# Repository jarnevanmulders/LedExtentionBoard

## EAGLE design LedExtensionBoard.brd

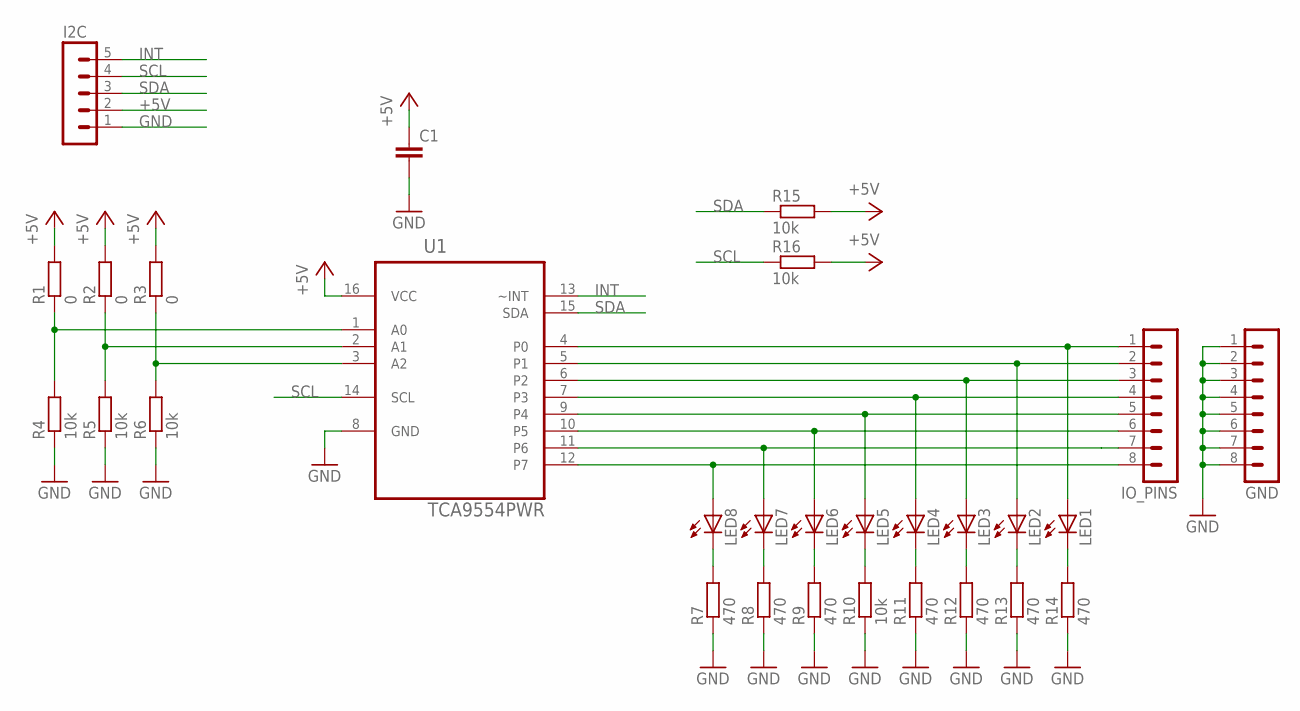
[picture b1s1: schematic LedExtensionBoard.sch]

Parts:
C1: C-EUC0805; C0805
GND: MA08-1
I2C: MA05-1
IO_PINS: MA08-1
LED1, LED2, LED3, LED4, LED5, LED6, LED7, LED8: LEDSML0805; SML0805
R1, R2, R3: 0; M1206
R4, R5, R6, R10, R15, R16: 10k; M0805
R7, R8, R9, R11, R12, R13, R14: 470; M0805
U1: TCA9554PWR; SOP65P640X120-16N

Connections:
+5V: C1.1, I2C.2, R1.2, R2.2, R3.2, R15.2, R16.2, U1.16 (VCC)
GND: C1.2, GND.1, GND.2, GND.3, GND.4, GND.5, GND.6, GND.7, GND.8, I2C.1, R4.1, R5.1, R6.1, R7.1, R8.1, R9.1, R10.1, R11.1, R12.1, R13.1, R14.1, U1.8 (GND)
INT: I2C.5, U1.13 (~INT)
unnamed: IO_PINS.8, LED8.A, U1.12 (P7)
unnamed: IO_PINS.7, LED7.A, U1.11 (P6)
unnamed: IO_PINS.6, LED6.A, U1.10 (P5)
unnamed: IO_PINS.5, LED5.A, U1.9 (P4)
unnamed: IO_PINS.4, LED4.A, U1.7 (P3)
unnamed: IO_PINS.3, LED3.A, U1.6 (P2)
unnamed: IO_PINS.2, LED2.A, U1.5 (P1)
unnamed: IO_PINS.1, LED1.A, U1.4 (P0)
unnamed: LED8.C, R7.2
unnamed: LED7.C, R8.2
unnamed: LED6.C, R9.2
unnamed: R1.1, R4.2, U1.1 (A0)
unnamed: R2.1, R5.2, U1.2 (A1)
unnamed: R3.1, R6.2, U1.3 (A2)
unnamed: LED5.C, R10.2
unnamed: LED4.C, R11.2
unnamed: LED3.C, R12.2
unnamed: LED2.C, R13.2
unnamed: LED1.C, R14.2
SCL: I2C.4, R16.1, U1.14 (SCL)
SDA: I2C.3, R15.1, U1.15 (SDA)

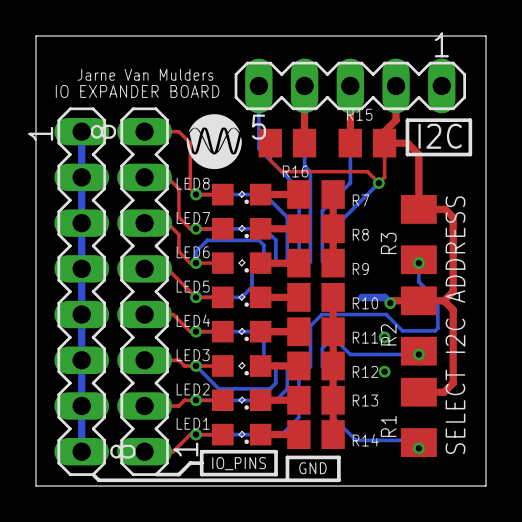
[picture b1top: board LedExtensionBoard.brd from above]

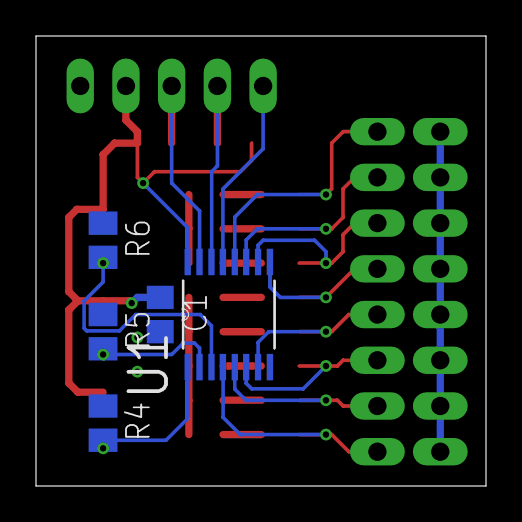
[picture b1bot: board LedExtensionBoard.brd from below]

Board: 2 copper layers, 25.0 x 25.0 mm, 29 parts (5 on the bottom side), 24 nets.

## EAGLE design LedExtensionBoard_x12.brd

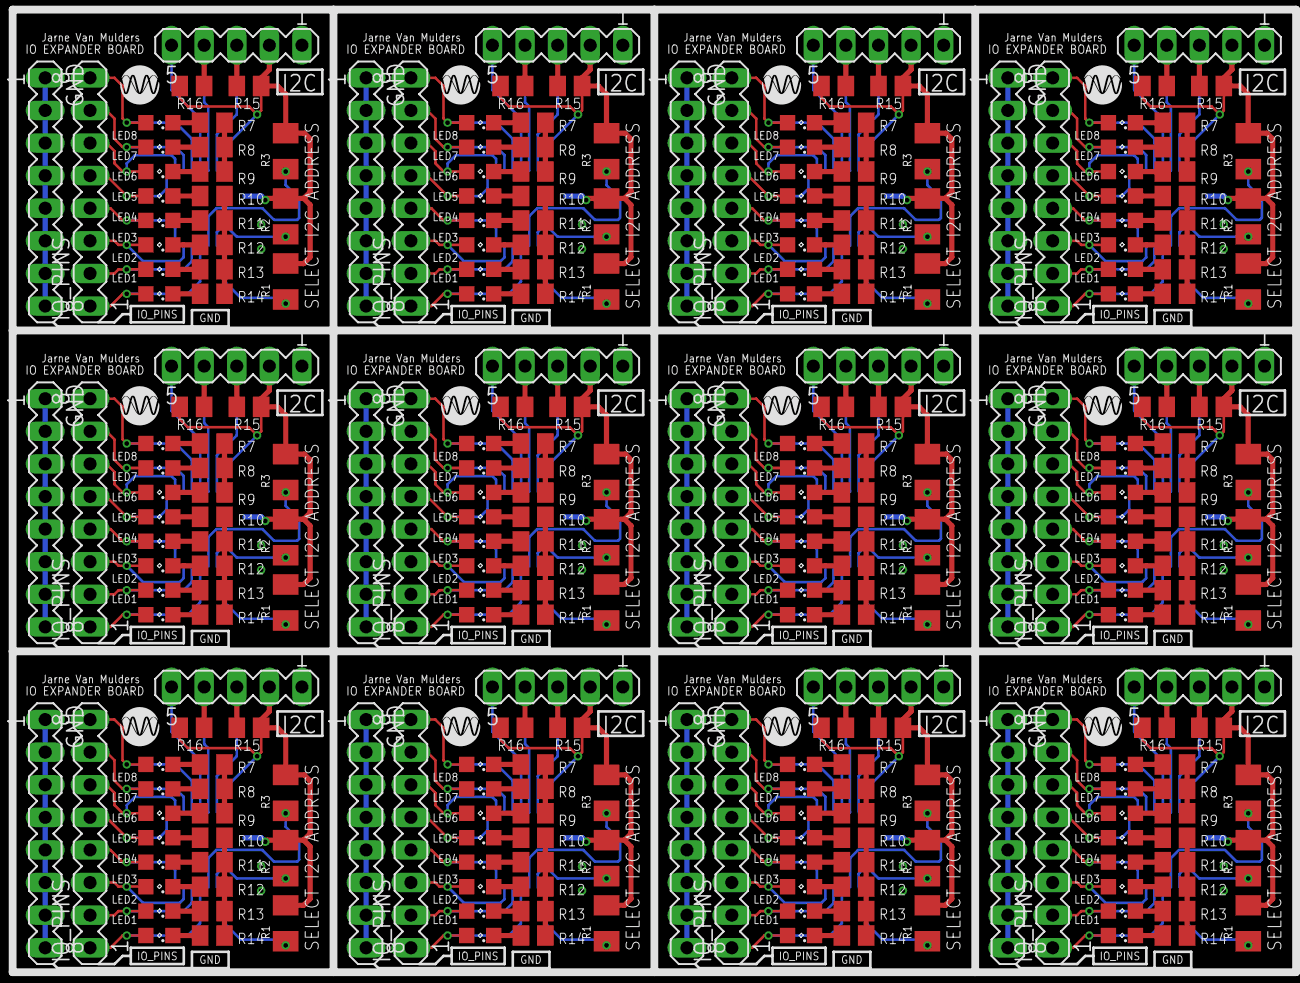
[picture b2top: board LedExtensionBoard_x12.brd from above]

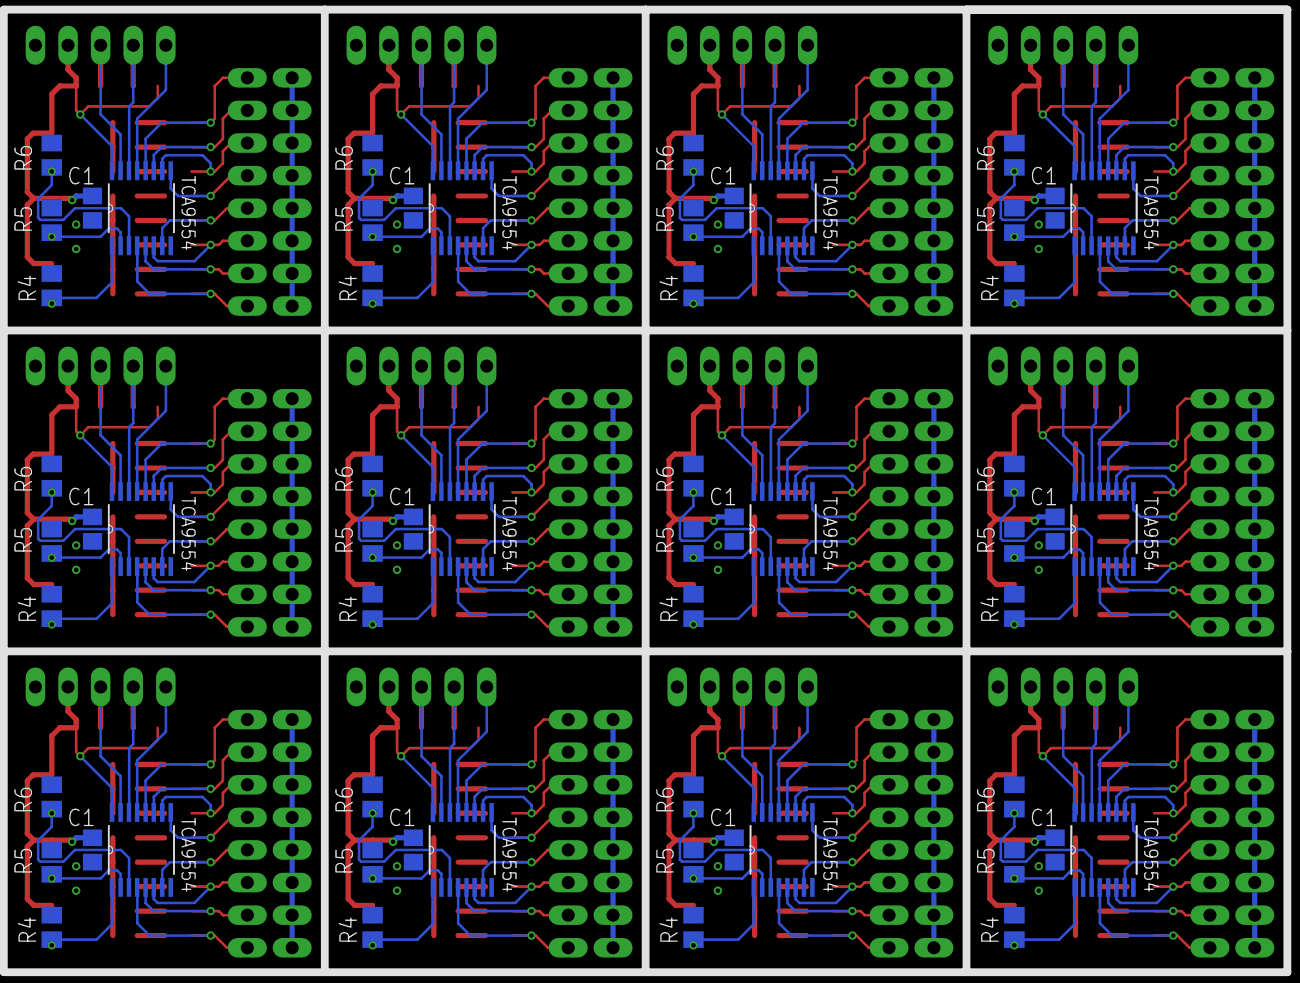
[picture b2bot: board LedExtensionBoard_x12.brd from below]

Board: 2 copper layers, 348 parts (60 on the bottom side), 288 nets.

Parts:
C1, C2, C3, C4, C5, C6, C7, C8, C9, C10, C11, C12: C0805
GND, GND1, GND2, GND3, GND4, GND5, GND6, GND7, GND8, GND9, GND10, GND11: MA08-1
I2C, I2C1, I2C2, I2C3, I2C4, I2C5, I2C6, I2C7, I2C8, I2C9, I2C10, I2C11: MA05-1
IO_PINS, IO_PINS1, IO_PINS2, IO_PINS3, IO_PINS4, IO_PINS5, IO_PINS6, IO_PINS7, IO_PINS8, IO_PINS9, IO_PINS10, IO_PINS11: MA08-1
LED1, LED2, LED3, LED4, LED5, LED6, LED7, LED8, LED9, LED10, LED11, LED12, LED13, LED14, LED15, LED16, LED17, LED18, LED19, LED20, LED21, LED22, LED23, LED24, LED25, LED26, LED27, LED28, LED29, LED30, LED31, LED32, LED33, LED34, LED35, LED36, LED37, LED38, LED39, LED40, LED41, LED42, LED43, LED44, LED45, LED46, LED47, LED48, LED49, LED50, LED51, LED52, LED53, LED54, LED55, LED56, LED57, LED58, LED59, LED60, LED61, LED62, LED63, LED64, LED65, LED66, LED67, LED68, LED69, LED70, LED71, LED72, LED73, LED74, LED75, LED76, LED77, LED78, LED79, LED80, LED81, LED82, LED83, LED84, LED85, LED86, LED87, LED88, LED89, LED90, LED91, LED92, LED93, LED94, LED95, LED96: SML0805
R1, R2, R3, R17, R23, R24, R33, R39, R40, R49, R55, R56, R65, R71, R72, R81, R87, R88, R97, R103, R104, R113, R119, R120, R129, R135, R136, R145, R151, R152, R161, R167, R168, R177, R183, R184: 0; M1206
R4, R5, R6, R10, R15, R16, R18, R25, R26, R27, R31, R32, R34, R41, R42, R43, R47, R48, R50, R57, R58, R59, R63, R64, R66, R73, R74, R75, R79, R80, R82, R89, R90, R91, R95, R96, R98, R105, R106, R107, R111, R112, R114, R121, R122, R123, R127, R128, R130, R137, R138, R139, R143, R144, R146, R153, R154, R155, R159, R160, R162, R169, R170, R171, R175, R176, R178, R185, R186, R187, R191, R192: 10k; M0805
R7, R8, R9, R11, R12, R13, R14, R19, R20, R21, R22, R28, R29, R30, R35, R36, R37, R38, R44, R45, R46, R51, R52, R53, R54, R60, R61, R62, R67, R68, R69, R70, R76, R77, R78, R83, R84, R85, R86, R92, R93, R94, R99, R100, R101, R102, R108, R109, R110, R115, R116, R117, R118, R124, R125, R126, R131, R132, R133, R134, R140, R141, R142, R147, R148, R149, R150, R156, R157, R158, R163, R164, R165, R166, R172, R173, R174, R179, R180, R181, R182, R188, R189, R190: 470; M0805
U1, U2, U3, U4, U5, U6, U7, U8, U9, U10, U11, U12: TCA9554PWR; SOP65P640X120-16N

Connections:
+5V: C1.1, I2C.2, R1.2, R2.2, R3.2, R15.2, R16.2, U1.16
+5V1: C2.1, I2C1.2, R17.2, R23.2, R24.2, R31.2, R32.2, U2.16
+5V2: C3.1, I2C2.2, R33.2, R39.2, R40.2, R47.2, R48.2, U3.16
+5V3: C4.1, I2C3.2, R49.2, R55.2, R56.2, R63.2, R64.2, U4.16
+5V4: C5.1, I2C4.2, R65.2, R71.2, R72.2, R79.2, R80.2, U5.16
+5V5: C6.1, I2C5.2, R81.2, R87.2, R88.2, R95.2, R96.2, U6.16
+5V6: C7.1, I2C6.2, R97.2, R103.2, R104.2, R111.2, R112.2, U7.16
+5V7: C8.1, I2C7.2, R113.2, R119.2, R120.2, R127.2, R128.2, U8.16
+5V8: C9.1, I2C8.2, R129.2, R135.2, R136.2, R143.2, R144.2, U9.16
+5V9: C10.1, I2C9.2, R145.2, R151.2, R152.2, R159.2, R160.2, U10.16
+5V10: C11.1, I2C10.2, R161.2, R167.2, R168.2, R175.2, R176.2, U11.16
+5V11: C12.1, I2C11.2, R177.2, R183.2, R184.2, R191.2, R192.2, U12.16
GND: C1.2, GND.1, GND.2, GND.3, GND.4, GND.5, GND.6, GND.7, GND.8, I2C.1, R4.1, R5.1, R6.1, R7.1, R8.1, R9.1, R10.1, R11.1, R12.1, R13.1, R14.1, U1.8
GND1: C2.2, GND1.1, GND1.2, GND1.3, GND1.4, GND1.5, GND1.6, GND1.7, GND1.8, I2C1.1, R18.1, R19.1, R20.1, R21.1, R22.1, R25.1, R26.1, R27.1, R28.1, R29.1, R30.1, U2.8
GND2: C3.2, GND2.1, GND2.2, GND2.3, GND2.4, GND2.5, GND2.6, GND2.7, GND2.8, I2C2.1, R34.1, R35.1, R36.1, R37.1, R38.1, R41.1, R42.1, R43.1, R44.1, R45.1, R46.1, U3.8
GND3: C4.2, GND3.1, GND3.2, GND3.3, GND3.4, GND3.5, GND3.6, GND3.7, GND3.8, I2C3.1, R50.1, R51.1, R52.1, R53.1, R54.1, R57.1, R58.1, R59.1, R60.1, R61.1, R62.1, U4.8
GND4: C5.2, GND4.1, GND4.2, GND4.3, GND4.4, GND4.5, GND4.6, GND4.7, GND4.8, I2C4.1, R66.1, R67.1, R68.1, R69.1, R70.1, R73.1, R74.1, R75.1, R76.1, R77.1, R78.1, U5.8
GND5: C6.2, GND5.1, GND5.2, GND5.3, GND5.4, GND5.5, GND5.6, GND5.7, GND5.8, I2C5.1, R82.1, R83.1, R84.1, R85.1, R86.1, R89.1, R90.1, R91.1, R92.1, R93.1, R94.1, U6.8
GND6: C7.2, GND6.1, GND6.2, GND6.3, GND6.4, GND6.5, GND6.6, GND6.7, GND6.8, I2C6.1, R98.1, R99.1, R100.1, R101.1, R102.1, R105.1, R106.1, R107.1, R108.1, R109.1, R110.1, U7.8
GND7: C8.2, GND7.1, GND7.2, GND7.3, GND7.4, GND7.5, GND7.6, GND7.7, GND7.8, I2C7.1, R114.1, R115.1, R116.1, R117.1, R118.1, R121.1, R122.1, R123.1, R124.1, R125.1, R126.1, U8.8
GND8: C9.2, GND8.1, GND8.2, GND8.3, GND8.4, GND8.5, GND8.6, GND8.7, GND8.8, I2C8.1, R130.1, R131.1, R132.1, R133.1, R134.1, R137.1, R138.1, R139.1, R140.1, R141.1, R142.1, U9.8
GND9: C10.2, GND9.1, GND9.2, GND9.3, GND9.4, GND9.5, GND9.6, GND9.7, GND9.8, I2C9.1, R146.1, R147.1, R148.1, R149.1, R150.1, R153.1, R154.1, R155.1, R156.1, R157.1, R158.1, U10.8
GND10: C11.2, GND10.1, GND10.2, GND10.3, GND10.4, GND10.5, GND10.6, GND10.7, GND10.8, I2C10.1, R162.1, R163.1, R164.1, R165.1, R166.1, R169.1, R170.1, R171.1, R172.1, R173.1, R174.1, U11.8
GND11: C12.2, GND11.1, GND11.2, GND11.3, GND11.4, GND11.5, GND11.6, GND11.7, GND11.8, I2C11.1, R178.1, R179.1, R180.1, R181.1, R182.1, R185.1, R186.1, R187.1, R188.1, R189.1, R190.1, U12.8
INT: I2C.5, U1.13
INT1: I2C1.5, U2.13
INT2: I2C2.5, U3.13
INT3: I2C3.5, U4.13
INT4: I2C4.5, U5.13
INT5: I2C5.5, U6.13
INT6: I2C6.5, U7.13
INT7: I2C7.5, U8.13
INT8: I2C8.5, U9.13
INT9: I2C9.5, U10.13
INT10: I2C10.5, U11.13
INT11: I2C11.5, U12.13
unnamed: IO_PINS.8, LED8.A, U1.12
unnamed: IO_PINS.7, LED7.A, U1.11
unnamed: IO_PINS.6, LED6.A, U1.10
unnamed: IO_PINS.5, LED5.A, U1.9
unnamed: IO_PINS.4, LED4.A, U1.7
unnamed: IO_PINS.3, LED3.A, U1.6
unnamed: IO_PINS.2, LED2.A, U1.5
unnamed: IO_PINS.1, LED1.A, U1.4
unnamed: LED8.C, R7.2
unnamed: LED7.C, R8.2
unnamed: LED6.C, R9.2
unnamed: R1.1, R4.2, U1.1
unnamed: R2.1, R5.2, U1.2
unnamed: R3.1, R6.2, U1.3
unnamed: LED5.C, R10.2
unnamed: LED4.C, R11.2
unnamed: LED3.C, R12.2
unnamed: LED2.C, R13.2
unnamed: LED1.C, R14.2
unnamed: IO_PINS1.8, LED16.A, U2.12
unnamed: IO_PINS1.7, LED15.A, U2.11
unnamed: IO_PINS1.6, LED14.A, U2.10
unnamed: IO_PINS1.5, LED13.A, U2.9
unnamed: IO_PINS1.4, LED12.A, U2.7
unnamed: IO_PINS1.3, LED11.A, U2.6
unnamed: IO_PINS1.2, LED10.A, U2.5
unnamed: IO_PINS1.1, LED9.A, U2.4
unnamed: R17.1, R25.2, U2.1
unnamed: R23.1, R26.2, U2.2
unnamed: R24.1, R27.2, U2.3
unnamed: LED16.C, R28.2
unnamed: LED15.C, R29.2
unnamed: LED14.C, R30.2
unnamed: LED13.C, R18.2
unnamed: LED12.C, R19.2
unnamed: LED11.C, R20.2
unnamed: LED10.C, R21.2
unnamed: LED9.C, R22.2
unnamed: IO_PINS2.8, LED24.A, U3.12
unnamed: IO_PINS2.7, LED23.A, U3.11
unnamed: IO_PINS2.6, LED22.A, U3.10
unnamed: IO_PINS2.5, LED21.A, U3.9
unnamed: IO_PINS2.4, LED20.A, U3.7
unnamed: IO_PINS2.3, LED19.A, U3.6
unnamed: IO_PINS2.2, LED18.A, U3.5
unnamed: IO_PINS2.1, LED17.A, U3.4
unnamed: R33.1, R41.2, U3.1
unnamed: R39.1, R42.2, U3.2
unnamed: R40.1, R43.2, U3.3
unnamed: LED24.C, R44.2
unnamed: LED23.C, R45.2
unnamed: LED22.C, R46.2
unnamed: LED21.C, R34.2
unnamed: LED20.C, R35.2
unnamed: LED19.C, R36.2
unnamed: LED18.C, R37.2
unnamed: LED17.C, R38.2
unnamed: IO_PINS3.8, LED32.A, U4.12
unnamed: IO_PINS3.7, LED31.A, U4.11
unnamed: IO_PINS3.6, LED30.A, U4.10
unnamed: IO_PINS3.5, LED29.A, U4.9
unnamed: IO_PINS3.4, LED28.A, U4.7
unnamed: IO_PINS3.3, LED27.A, U4.6
unnamed: IO_PINS3.2, LED26.A, U4.5
unnamed: IO_PINS3.1, LED25.A, U4.4
unnamed: R49.1, R57.2, U4.1
unnamed: R55.1, R58.2, U4.2
unnamed: R56.1, R59.2, U4.3
unnamed: LED32.C, R60.2
unnamed: LED31.C, R61.2
unnamed: LED30.C, R62.2
unnamed: LED29.C, R50.2
unnamed: LED28.C, R51.2
unnamed: LED27.C, R52.2
unnamed: LED26.C, R53.2
unnamed: LED25.C, R54.2
unnamed: IO_PINS4.8, LED40.A, U5.12
unnamed: IO_PINS4.7, LED39.A, U5.11
unnamed: IO_PINS4.6, LED38.A, U5.10
unnamed: IO_PINS4.5, LED37.A, U5.9
unnamed: IO_PINS4.4, LED36.A, U5.7
unnamed: IO_PINS4.3, LED35.A, U5.6
unnamed: IO_PINS4.2, LED34.A, U5.5
unnamed: IO_PINS4.1, LED33.A, U5.4
unnamed: R65.1, R73.2, U5.1
unnamed: R71.1, R74.2, U5.2
unnamed: R72.1, R75.2, U5.3
unnamed: LED40.C, R76.2
unnamed: LED39.C, R77.2
unnamed: LED38.C, R78.2
unnamed: LED37.C, R66.2
unnamed: LED36.C, R67.2
unnamed: LED35.C, R68.2
unnamed: LED34.C, R69.2
unnamed: LED33.C, R70.2
unnamed: IO_PINS5.8, LED48.A, U6.12
unnamed: IO_PINS5.7, LED47.A, U6.11
unnamed: IO_PINS5.6, LED46.A, U6.10
unnamed: IO_PINS5.5, LED45.A, U6.9
unnamed: IO_PINS5.4, LED44.A, U6.7
unnamed: IO_PINS5.3, LED43.A, U6.6
unnamed: IO_PINS5.2, LED42.A, U6.5
unnamed: IO_PINS5.1, LED41.A, U6.4
unnamed: R81.1, R89.2, U6.1
unnamed: R87.1, R90.2, U6.2
unnamed: R88.1, R91.2, U6.3
unnamed: LED48.C, R92.2
unnamed: LED47.C, R93.2
unnamed: LED46.C, R94.2
unnamed: LED45.C, R82.2
unnamed: LED44.C, R83.2
unnamed: LED43.C, R84.2
unnamed: LED42.C, R85.2
unnamed: LED41.C, R86.2
unnamed: IO_PINS6.8, LED56.A, U7.12
unnamed: IO_PINS6.7, LED55.A, U7.11
unnamed: IO_PINS6.6, LED54.A, U7.10
unnamed: IO_PINS6.5, LED53.A, U7.9
unnamed: IO_PINS6.4, LED52.A, U7.7
unnamed: IO_PINS6.3, LED51.A, U7.6
unnamed: IO_PINS6.2, LED50.A, U7.5
unnamed: IO_PINS6.1, LED49.A, U7.4
unnamed: R97.1, R105.2, U7.1
unnamed: R103.1, R106.2, U7.2
unnamed: R104.1, R107.2, U7.3
unnamed: LED56.C, R108.2
unnamed: LED55.C, R109.2
unnamed: LED54.C, R110.2
unnamed: LED53.C, R98.2
unnamed: LED52.C, R99.2
unnamed: LED51.C, R100.2
unnamed: LED50.C, R101.2
unnamed: LED49.C, R102.2
unnamed: IO_PINS7.8, LED64.A, U8.12
unnamed: IO_PINS7.7, LED63.A, U8.11
unnamed: IO_PINS7.6, LED62.A, U8.10
unnamed: IO_PINS7.5, LED61.A, U8.9
unnamed: IO_PINS7.4, LED60.A, U8.7
unnamed: IO_PINS7.3, LED59.A, U8.6
unnamed: IO_PINS7.2, LED58.A, U8.5
unnamed: IO_PINS7.1, LED57.A, U8.4
unnamed: R113.1, R121.2, U8.1
unnamed: R119.1, R122.2, U8.2
unnamed: R120.1, R123.2, U8.3
unnamed: LED64.C, R124.2
unnamed: LED63.C, R125.2
unnamed: LED62.C, R126.2
unnamed: LED61.C, R114.2
unnamed: LED60.C, R115.2
unnamed: LED59.C, R116.2
unnamed: LED58.C, R117.2
unnamed: LED57.C, R118.2
unnamed: IO_PINS8.8, LED72.A, U9.12
unnamed: IO_PINS8.7, LED71.A, U9.11
unnamed: IO_PINS8.6, LED70.A, U9.10
unnamed: IO_PINS8.5, LED69.A, U9.9
unnamed: IO_PINS8.4, LED68.A, U9.7
unnamed: IO_PINS8.3, LED67.A, U9.6
unnamed: IO_PINS8.2, LED66.A, U9.5
unnamed: IO_PINS8.1, LED65.A, U9.4
unnamed: R129.1, R137.2, U9.1
unnamed: R135.1, R138.2, U9.2
unnamed: R136.1, R139.2, U9.3
unnamed: LED72.C, R140.2
unnamed: LED71.C, R141.2
unnamed: LED70.C, R142.2
unnamed: LED69.C, R130.2
unnamed: LED68.C, R131.2
unnamed: LED67.C, R132.2
unnamed: LED66.C, R133.2
unnamed: LED65.C, R134.2
unnamed: IO_PINS9.8, LED80.A, U10.12
unnamed: IO_PINS9.7, LED79.A, U10.11
unnamed: IO_PINS9.6, LED78.A, U10.10
unnamed: IO_PINS9.5, LED77.A, U10.9
unnamed: IO_PINS9.4, LED76.A, U10.7
unnamed: IO_PINS9.3, LED75.A, U10.6
unnamed: IO_PINS9.2, LED74.A, U10.5
unnamed: IO_PINS9.1, LED73.A, U10.4
unnamed: R145.1, R153.2, U10.1
unnamed: R151.1, R154.2, U10.2
unnamed: R152.1, R155.2, U10.3
unnamed: LED80.C, R156.2
unnamed: LED79.C, R157.2
unnamed: LED78.C, R158.2
unnamed: LED77.C, R146.2
unnamed: LED76.C, R147.2
unnamed: LED75.C, R148.2
unnamed: LED74.C, R149.2
unnamed: LED73.C, R150.2
unnamed: IO_PINS10.8, LED88.A, U11.12
unnamed: IO_PINS10.7, LED87.A, U11.11
unnamed: IO_PINS10.6, LED86.A, U11.10
unnamed: IO_PINS10.5, LED85.A, U11.9
unnamed: IO_PINS10.4, LED84.A, U11.7
unnamed: IO_PINS10.3, LED83.A, U11.6
unnamed: IO_PINS10.2, LED82.A, U11.5
unnamed: IO_PINS10.1, LED81.A, U11.4
unnamed: R161.1, R169.2, U11.1
unnamed: R167.1, R170.2, U11.2
unnamed: R168.1, R171.2, U11.3
unnamed: LED88.C, R172.2
unnamed: LED87.C, R173.2
unnamed: LED86.C, R174.2
unnamed: LED85.C, R162.2
unnamed: LED84.C, R163.2
unnamed: LED83.C, R164.2
unnamed: LED82.C, R165.2
unnamed: LED81.C, R166.2
unnamed: IO_PINS11.8, LED96.A, U12.12
unnamed: IO_PINS11.7, LED95.A, U12.11
unnamed: IO_PINS11.6, LED94.A, U12.10
unnamed: IO_PINS11.5, LED93.A, U12.9
unnamed: IO_PINS11.4, LED92.A, U12.7
unnamed: IO_PINS11.3, LED91.A, U12.6
unnamed: IO_PINS11.2, LED90.A, U12.5
unnamed: IO_PINS11.1, LED89.A, U12.4
unnamed: R177.1, R185.2, U12.1
unnamed: R183.1, R186.2, U12.2
unnamed: R184.1, R187.2, U12.3
unnamed: LED96.C, R188.2
unnamed: LED95.C, R189.2
unnamed: LED94.C, R190.2
unnamed: LED93.C, R178.2
unnamed: LED92.C, R179.2
unnamed: LED91.C, R180.2
unnamed: LED90.C, R181.2
unnamed: LED89.C, R182.2
SCL: I2C.4, R16.1, U1.14
SCL1: I2C1.4, R32.1, U2.14
SCL2: I2C2.4, R48.1, U3.14
SCL3: I2C3.4, R64.1, U4.14
SCL4: I2C4.4, R80.1, U5.14
SCL5: I2C5.4, R96.1, U6.14
SCL6: I2C6.4, R112.1, U7.14
SCL7: I2C7.4, R128.1, U8.14
SCL8: I2C8.4, R144.1, U9.14
SCL9: I2C9.4, R160.1, U10.14
SCL10: I2C10.4, R176.1, U11.14
SCL11: I2C11.4, R192.1, U12.14
SDA: I2C.3, R15.1, U1.15
SDA1: I2C1.3, R31.1, U2.15
SDA2: I2C2.3, R47.1, U3.15
SDA3: I2C3.3, R63.1, U4.15
SDA4: I2C4.3, R79.1, U5.15
SDA5: I2C5.3, R95.1, U6.15
SDA6: I2C6.3, R111.1, U7.15
SDA7: I2C7.3, R127.1, U8.15
SDA8: I2C8.3, R143.1, U9.15
SDA9: I2C9.3, R159.1, U10.15
SDA10: I2C10.3, R175.1, U11.15
SDA11: I2C11.3, R191.1, U12.15

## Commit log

2019-01-17 update x1 & x12
